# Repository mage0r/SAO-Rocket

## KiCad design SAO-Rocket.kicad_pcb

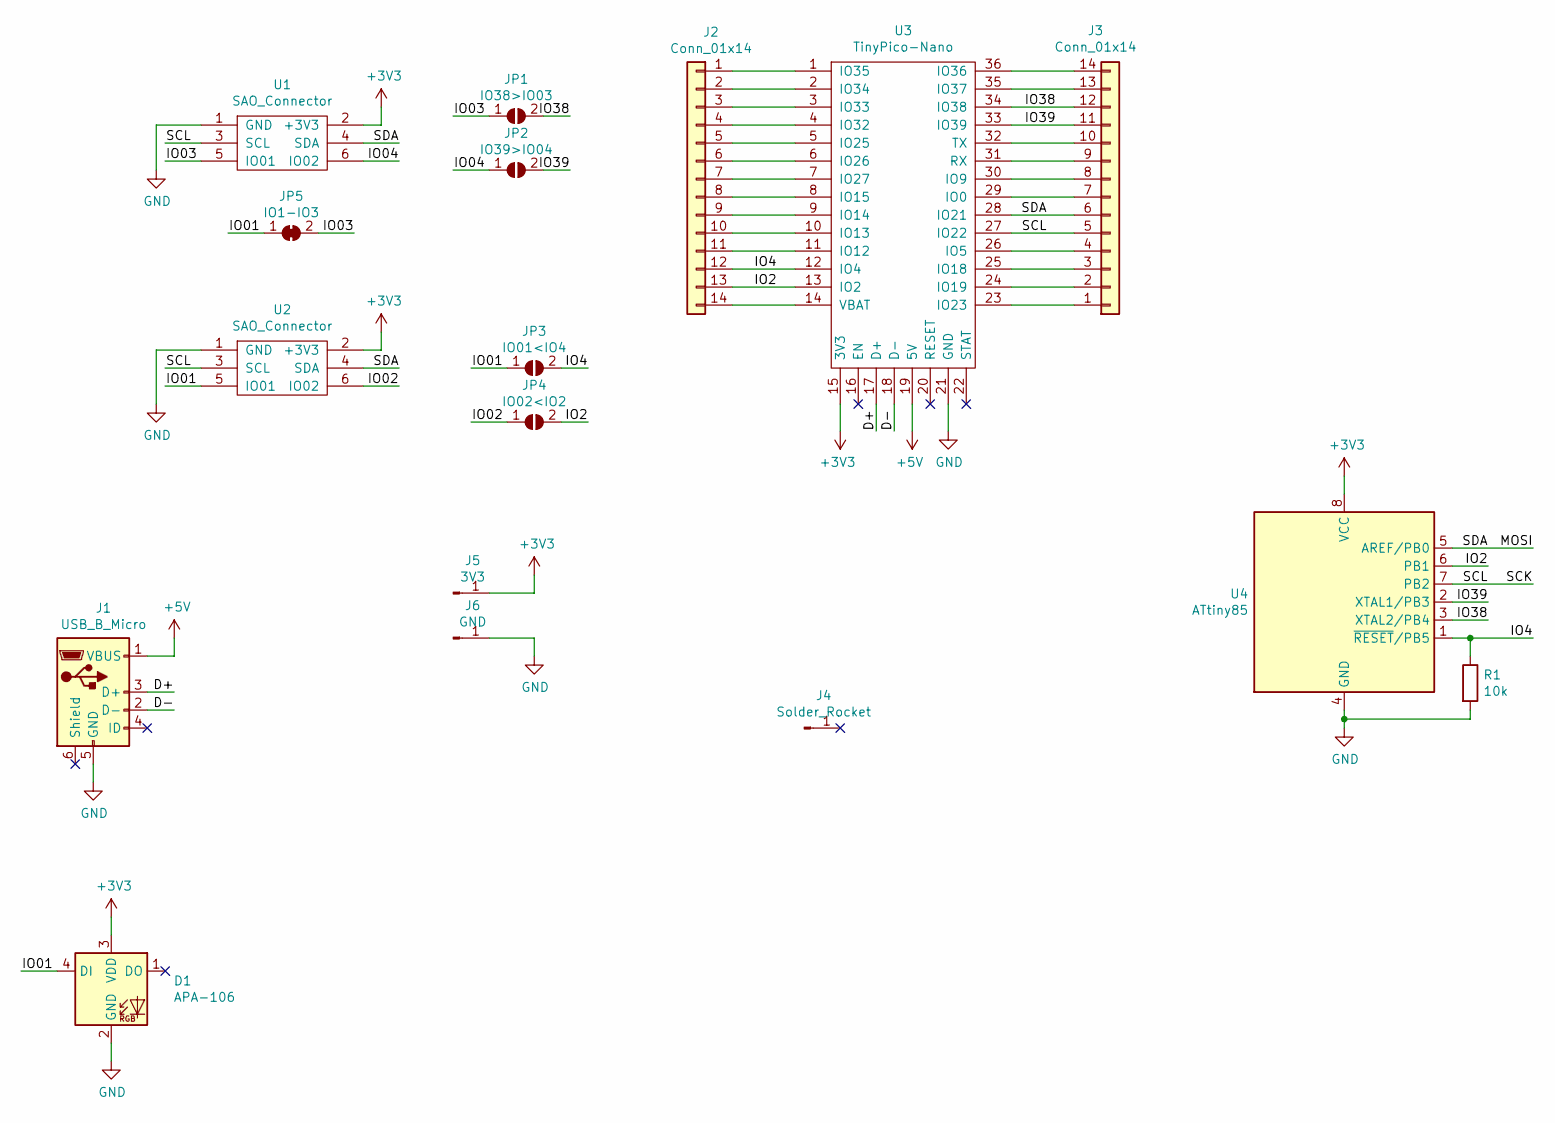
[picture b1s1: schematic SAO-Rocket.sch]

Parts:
D1: APA-106; LED_D5.0mm-4_RGB
J1: USB_B_Micro; USB-MICRO-5pin_PTHMOUNT-Amphenol.10118194-0001LF
J2, J3: Conn_01x14; PinHeader_1x14_P1.27mm_Vertical
J4: Solder_Rocket; solder-rocket-small
J5: 3V3; PinHeader_1x01_P1.27mm_Vertical
J6: GND; PinHeader_1x01_P1.27mm_Vertical
JP1: IO38>IO03; SolderJumper-2_P1.3mm_Open_RoundedPad1.0x1.5mm
JP2: IO39>IO04; SolderJumper-2_P1.3mm_Open_RoundedPad1.0x1.5mm
JP3: IO01<IO4; SolderJumper-2_P1.3mm_Open_RoundedPad1.0x1.5mm
JP4: IO02<IO2; SolderJumper-2_P1.3mm_Open_RoundedPad1.0x1.5mm
JP5: IO1-IO3; SolderJumper-2_P1.3mm_Bridged2Bar_Pad1.0x1.5mm
R1: 10k; R_0603_1608Metric_Pad1.05x0.95mm_HandSolder
U1, U2: SAO_Connector
U3: TinyPico-Nano; TinyPICO_Nano
U4: ATtiny85; SOIJ-8_5.3x5.3mm_P1.27mm

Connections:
+3V3: D1.3 (VDD), J5.1, U1.2 (+3V3), U2.2 (+3V3), U3.15 (3V3), U4.8 (VCC)
+5V: J1.1 (VBUS), U3.19 (5V)
/D+: J1.3 (D+), U3.17 (D+)
/D-: J1.2 (D-), U3.18 (D-)
/IO01: D1.4 (DI), JP3.1 (A), JP5.1 (A), U2.5 (IO01)
/IO2: J2.13, JP4.2 (B), U3.13 (IO2), U4.6 (PB1)
/IO02: JP4.1 (A), U2.6 (IO02)
/IO03: JP1.1 (A), JP5.2 (B), U1.5 (IO01)
/IO4: J2.12, JP3.2 (B), R1.1, U3.12 (IO4), U4.1 (~RESET~/PB5)
/IO04: JP2.1 (A), U1.6 (IO02)
/IO38: J3.12, JP1.2 (B), U3.34 (IO38), U4.3 (XTAL2/PB4)
/IO39: J3.11, JP2.2 (B), U3.33 (IO39), U4.2 (XTAL1/PB3)
/MOSI: J3.6, U1.4 (SDA), U2.4 (SDA), U3.28 (IO21), U4.5 (AREF/PB0)
/SCK: J3.5, U1.3 (SCL), U2.3 (SCL), U3.27 (IO22), U4.7 (PB2)
GND: D1.2 (GND), J1.5 (GND), J6.1, R1.2, U1.1 (GND), U2.1 (GND), U3.21 (GND), U4.4 (GND)
unnamed: J2.1, U3.1 (IO35)
unnamed: J2.2, U3.2 (IO34)
unnamed: J2.3, U3.3 (IO33)
unnamed: J2.4, U3.4 (IO32)
unnamed: J2.5, U3.5 (IO25)
unnamed: J2.6, U3.6 (IO26)
unnamed: J2.7, U3.7 (IO27)
unnamed: J2.8, U3.8 (IO15)
unnamed: J2.9, U3.9 (IO14)
unnamed: J2.10, U3.10 (IO13)
unnamed: J2.11, U3.11 (IO12)
unnamed: J2.14, U3.14 (VBAT)
unnamed: J3.1, U3.23 (IO23)
unnamed: J3.2, U3.24 (IO19)
unnamed: J3.3, U3.25 (IO18)
unnamed: J3.4, U3.26 (IO5)
unnamed: J3.7, U3.29 (IO0)
unnamed: J3.8, U3.30 (IO9)
unnamed: J3.9, U3.31 (RX)
unnamed: J3.10, U3.32 (TX)
unnamed: J3.13, U3.35 (IO37)
unnamed: J3.14, U3.36 (IO36)

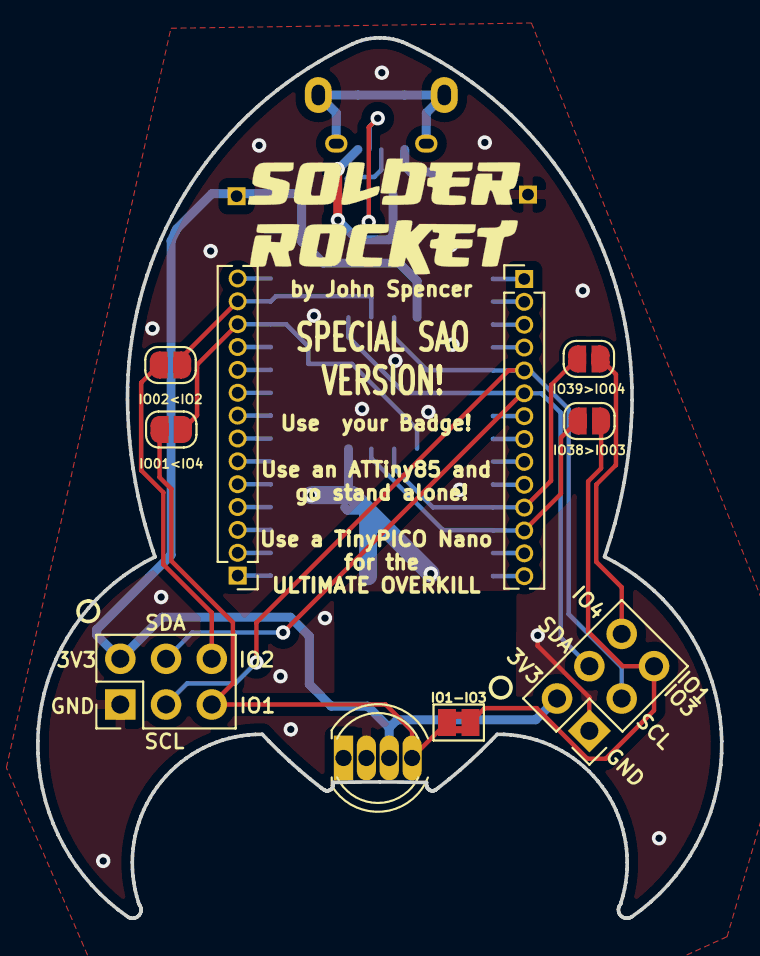
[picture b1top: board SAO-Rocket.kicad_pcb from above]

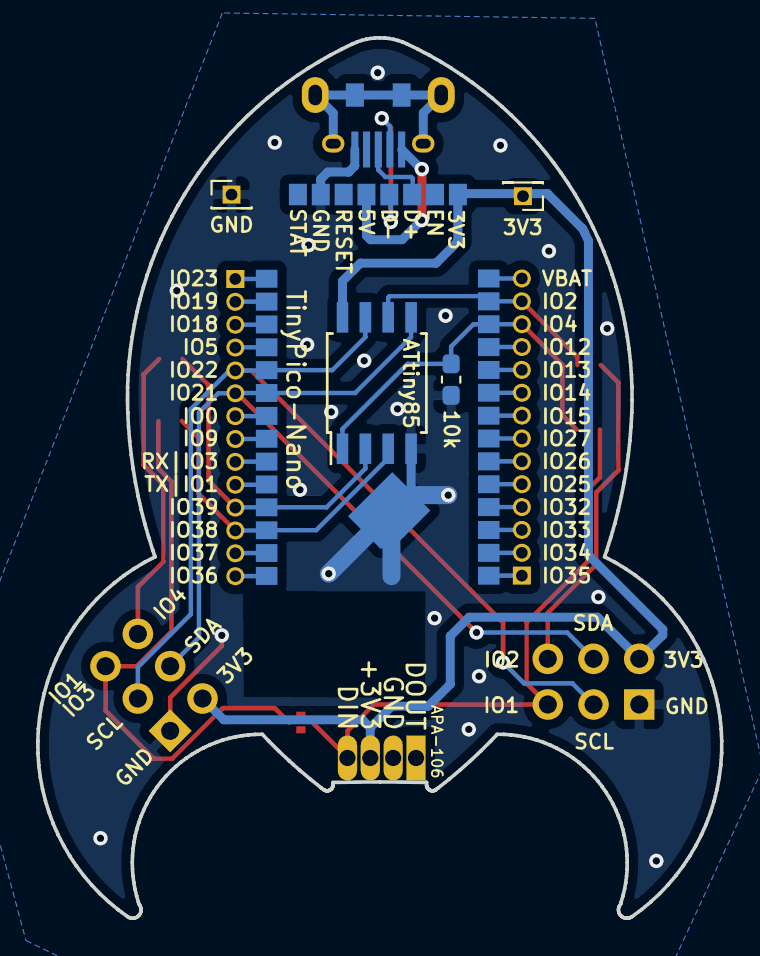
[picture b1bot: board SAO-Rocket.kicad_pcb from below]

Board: 2 copper layers, 38.0 x 48.9 mm, 17 parts (6 on the bottom side), 37 nets.

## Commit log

2021-01-30 :lollipop: Added .gitattributes & .gitignore files
2021-01-30 Inital version control upload
